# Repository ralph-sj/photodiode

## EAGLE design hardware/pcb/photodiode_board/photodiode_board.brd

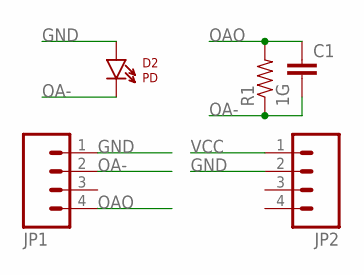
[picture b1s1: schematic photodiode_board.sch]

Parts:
C1: CAPPTH; CAP-PTH-SMALL
D2: PD; LTE-302
JP1, JP2: M04PTH; 1X04
R1: 1G; AXIAL-0.3

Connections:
GND: D2.A, JP1.1, JP2.2
OA-: C1.2, D2.C, JP1.2, R1.P$1 (1)
OAO: C1.1, JP1.4, R1.P$2 (2)
VCC: JP2.1

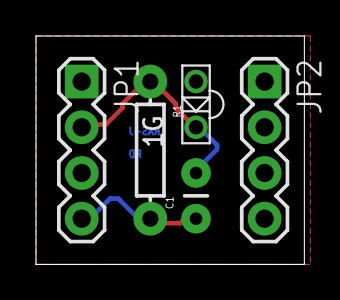
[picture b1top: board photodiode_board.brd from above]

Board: 2 copper layers, 14.9 x 12.7 mm, 5 parts (0 on the bottom side), 3 nets.

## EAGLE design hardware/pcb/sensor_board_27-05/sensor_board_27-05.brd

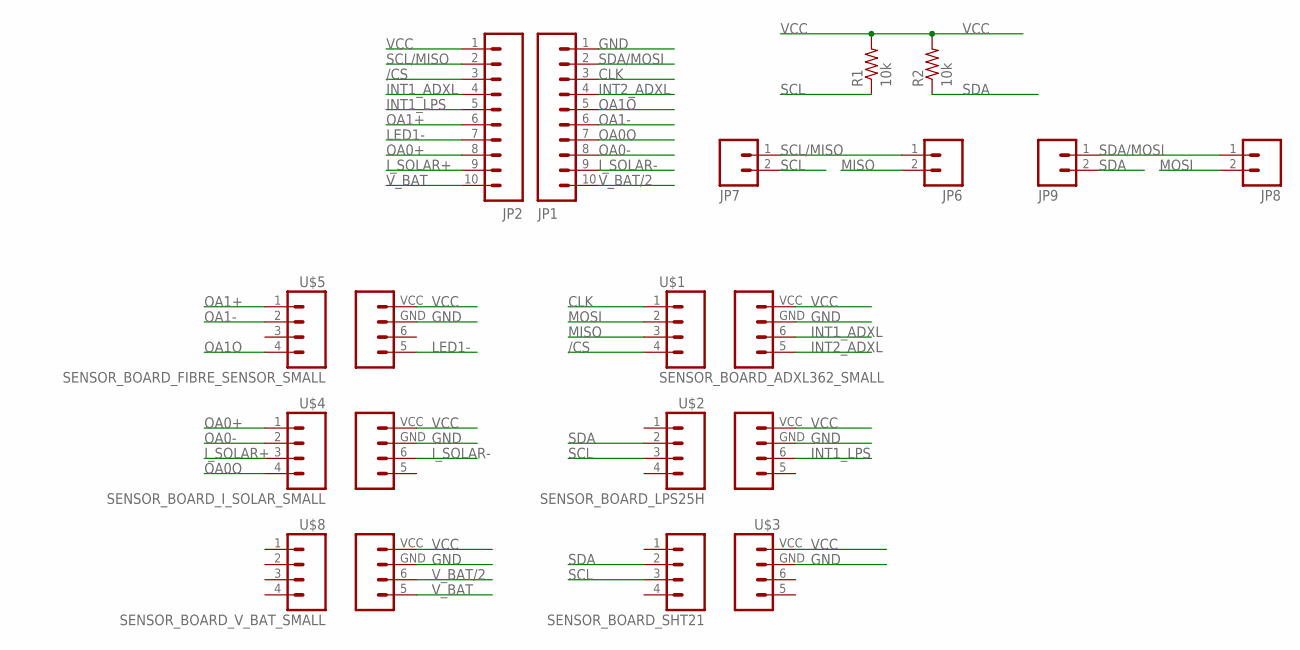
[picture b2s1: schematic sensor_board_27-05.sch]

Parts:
JP1, JP2: M10SILK_FEMALE_PTH; 1X10
JP6, JP7, JP8, JP9: M02PTH; 1X02
R1, R2: 10k; AXIAL-0.3
U$1: SENSOR_BOARD_ADXL362_SMALL; SENSOR_BOARD_GEN_SMALL
U$2: SENSOR_BOARD_LPS25H; SENSOR_BOARD_GEN
U$3: SENSOR_BOARD_SHT21; SENSOR_BOARD_GEN
U$4: SENSOR_BOARD_I_SOLAR_SMALL; SENSOR_BOARD_GEN_SMALL
U$5: SENSOR_BOARD_FIBRE_SENSOR_SMALL; SENSOR_BOARD_GEN_SMALL
U$8: SENSOR_BOARD_V_BAT_SMALL; SENSOR_BOARD_GEN_SMALL

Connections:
/CS: JP2.3, U$1.4 (/CS)
CLK: JP1.3, U$1.1 (CLK)
GND: JP1.1, U$1.GND, U$2.GND, U$3.GND, U$4.GND, U$5.GND, U$8.GND
INT1_ADXL: JP2.4, U$1.6 (INT1)
INT1_LPS: JP2.5, U$2.6 (INT1)
INT2_ADXL: JP1.4, U$1.5 (INT2)
I_SOLAR+: JP2.9, U$4.3 (I_SOLAR+)
I_SOLAR-: JP1.9, U$4.6 (I_SOLAR-)
LED1-: JP2.7, U$5.5 (LED-)
MISO: JP6.2, U$1.3 (MISO)
MOSI: JP8.2, U$1.2 (MOSI)
OA0+: JP2.8, U$4.1 (OA+)
OA0-: JP1.8, U$4.2 (OA-)
OA0O: JP1.7, U$4.4 (OAO)
OA1+: JP2.6, U$5.1 (OA+)
OA1-: JP1.6, U$5.2 (OA-)
OA1O: JP1.5, U$5.4 (OAO)
SCL: JP7.2, R1.P$1 (1), U$2.3 (SCL), U$3.3 (SCL)
SCL/MISO: JP2.2, JP6.1, JP7.1
SDA: JP9.2, R2.P$1 (1), U$2.2 (SDA), U$3.2 (SDA)
SDA/MOSI: JP1.2, JP8.1, JP9.1
VCC: JP2.1, R1.P$2 (2), R2.P$2 (2), U$1.VCC, U$2.VCC, U$3.VCC, U$4.VCC, U$5.VCC, U$8.VCC
V_BAT: JP2.10, U$8.5 (V_BAT)
V_BAT/2: JP1.10, U$8.6 (V_BAT/2)

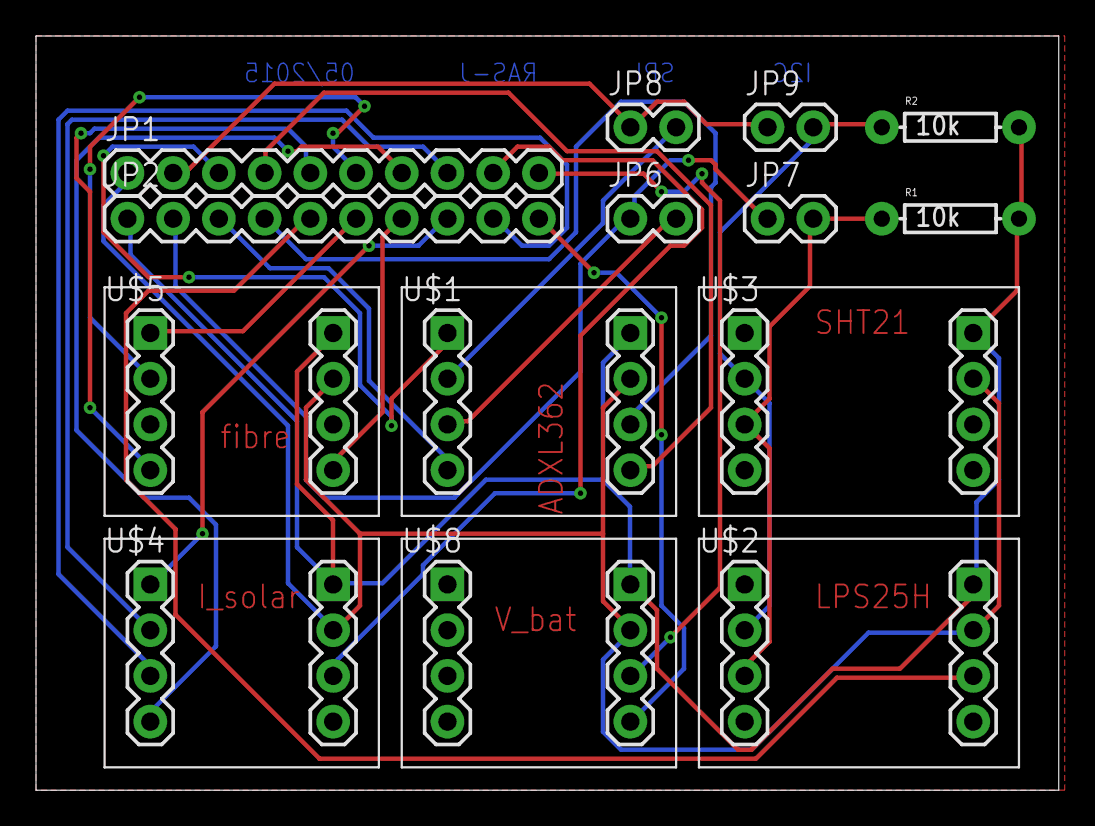
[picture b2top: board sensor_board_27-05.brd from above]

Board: 2 copper layers, 56.8 x 41.9 mm, 14 parts (0 on the bottom side), 24 nets.

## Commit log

2015-10-22 :lollipop: Added .gitattributes & .gitignore files
2015-10-23 CCS added
2015-10-23 CCS folder added
2015-10-23 Firmware created. Vpd appended to message. Data displayed through AP
2015-10-23 Deleted files removed.
2015-10-27 CCS firmware modified to TX data through COM port
2015-10-27 data folder added. Data gathered and analysed using matlab script
2015-10-30 Sensor Monitor updated to node ID in 0.00 for subnets of subsequent, envisaged, branch networks
2015-10-30 Data downloaded from server from previous test (till 27/10)
2015-10-30 added documents about development in docs folder
2015-10-30 node 2 server file created
2015-10-30 pi python file updated for new node numbering system and the addition of node 0.02

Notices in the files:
parts and their libraries:
SparkFun-Capacitors: Licensing: Creative Commons ShareAlike 4.0 International - https://creativecommons.org/licenses/by-sa/4.0
